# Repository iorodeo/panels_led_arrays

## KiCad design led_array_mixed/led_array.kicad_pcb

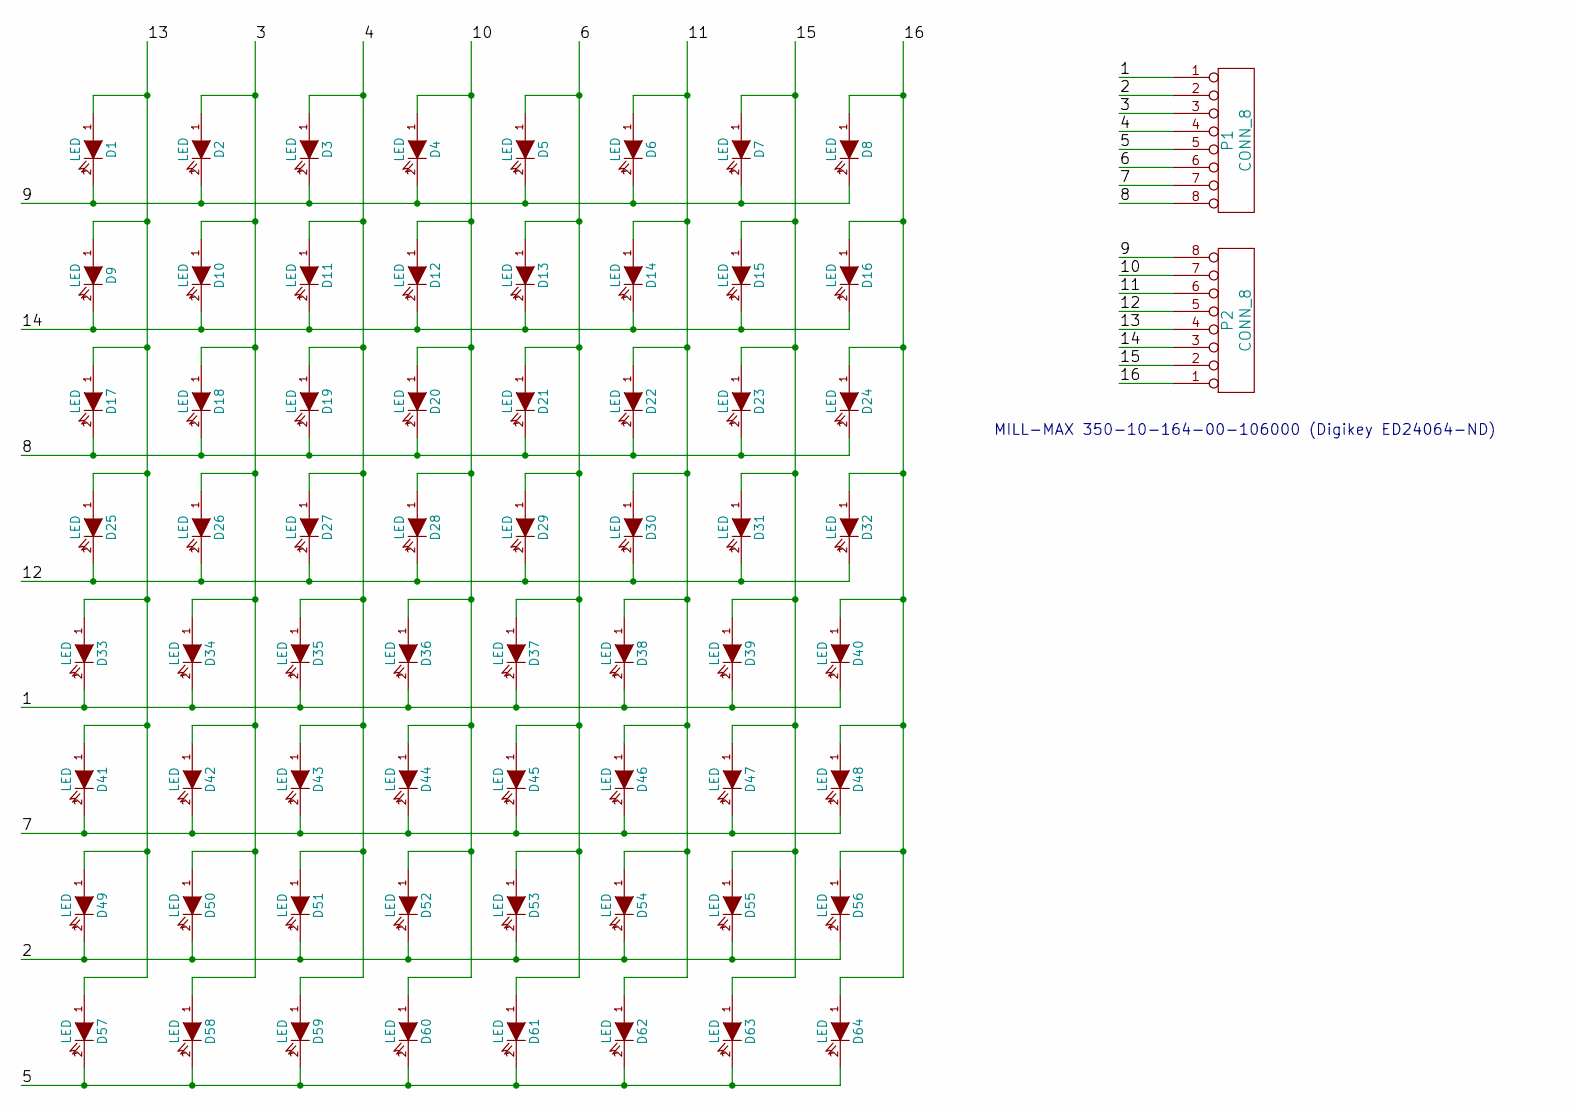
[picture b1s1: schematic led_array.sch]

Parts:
D1, D2, D3, D4, D5, D6, D7, D8, D9, D10, D11, D12, D13, D14, D15, D16, D17, D18, D19, D20, D21, D22, D23, D24, D25, D26, D27, D28, D29, D30, D31, D32, D33, D34, D35, D36, D37, D38, D39, D40, D41, D42, D43, D44, D45, D46, D47, D48, D49, D50, D51, D52, D53, D54, D55, D56, D57, D58, D59, D60, D61, D62, D63, D64: LED
P1, P2: CONN_8

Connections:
/1: D33.2 (K), D34.2 (K), D35.2 (K), D36.2 (K), D37.2 (K), D38.2 (K), D39.2 (K), D40.2 (K), P1.1
/2: D49.2 (K), D50.2 (K), D51.2 (K), D52.2 (K), D53.2 (K), D54.2 (K), D55.2 (K), D56.2 (K), P1.2
/3: D2.1 (A), D10.1 (A), D18.1 (A), D26.1 (A), D34.1 (A), D42.1 (A), D50.1 (A), D58.1 (A), P1.3
/4: D3.1 (A), D11.1 (A), D19.1 (A), D27.1 (A), D35.1 (A), D43.1 (A), D51.1 (A), D59.1 (A), P1.4
/5: D57.2 (K), D58.2 (K), D59.2 (K), D60.2 (K), D61.2 (K), D62.2 (K), D63.2 (K), D64.2 (K), P1.5
/6: D5.1 (A), D13.1 (A), D21.1 (A), D29.1 (A), D37.1 (A), D45.1 (A), D53.1 (A), D61.1 (A), P1.6
/7: D41.2 (K), D42.2 (K), D43.2 (K), D44.2 (K), D45.2 (K), D46.2 (K), D47.2 (K), D48.2 (K), P1.7
/8: D17.2 (K), D18.2 (K), D19.2 (K), D20.2 (K), D21.2 (K), D22.2 (K), D23.2 (K), D24.2 (K), P1.8
/9: D1.2 (K), D2.2 (K), D3.2 (K), D4.2 (K), D5.2 (K), D6.2 (K), D7.2 (K), D8.2 (K), P2.8
/10: D4.1 (A), D12.1 (A), D20.1 (A), D28.1 (A), D36.1 (A), D44.1 (A), D52.1 (A), D60.1 (A), P2.7
/11: D6.1 (A), D14.1 (A), D22.1 (A), D30.1 (A), D38.1 (A), D46.1 (A), D54.1 (A), D62.1 (A), P2.6
/12: D25.2 (K), D26.2 (K), D27.2 (K), D28.2 (K), D29.2 (K), D30.2 (K), D31.2 (K), D32.2 (K), P2.5
/13: D1.1 (A), D9.1 (A), D17.1 (A), D25.1 (A), D33.1 (A), D41.1 (A), D49.1 (A), D57.1 (A), P2.4
/14: D9.2 (K), D10.2 (K), D11.2 (K), D12.2 (K), D13.2 (K), D14.2 (K), D15.2 (K), D16.2 (K), P2.3
/15: D7.1 (A), D15.1 (A), D23.1 (A), D31.1 (A), D39.1 (A), D47.1 (A), D55.1 (A), D63.1 (A), P2.2
/16: D8.1 (A), D16.1 (A), D24.1 (A), D32.1 (A), D40.1 (A), D48.1 (A), D56.1 (A), D64.1 (A), P2.1

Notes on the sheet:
MILL-MAX 350-10-164-00-106000 (Digikey ED24064-ND)

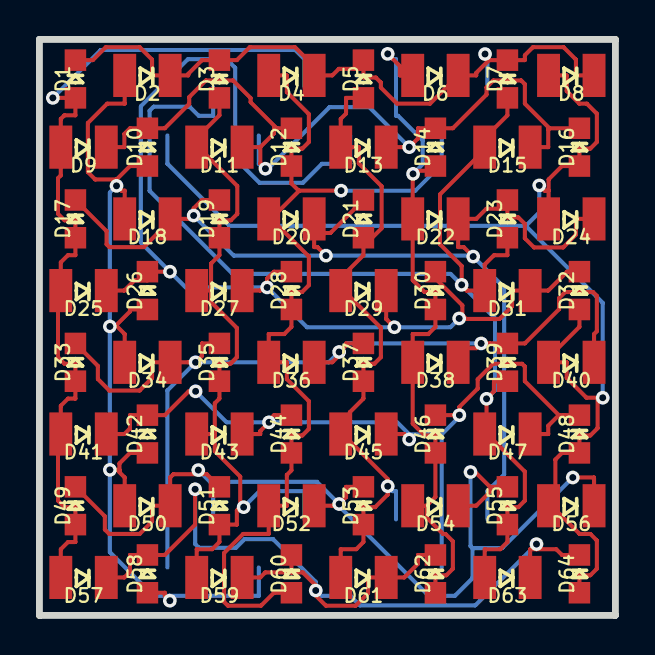
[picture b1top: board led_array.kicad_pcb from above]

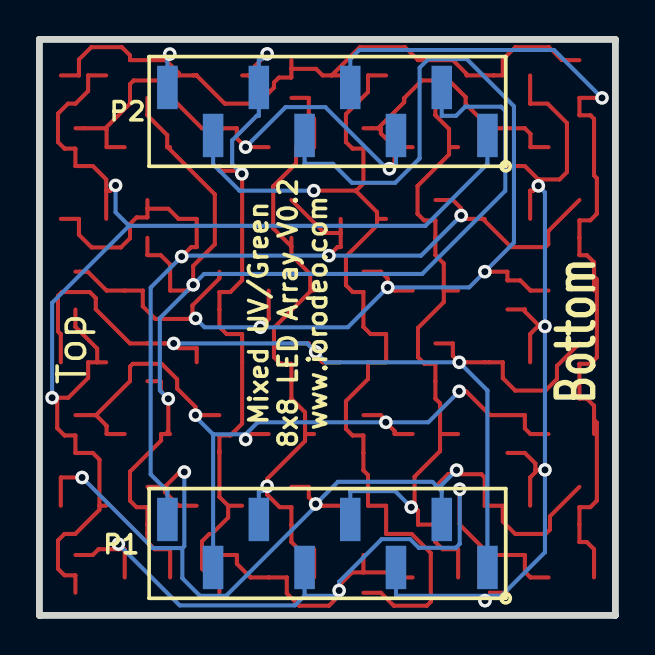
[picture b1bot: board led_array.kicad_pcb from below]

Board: 2 copper layers, 32.0 x 32.0 mm, 66 parts (2 on the bottom side), 16 nets.

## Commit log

2013-02-12 Project creation.
2013-02-12 Added license file.
2013-02-13 Fixed missing solder mask on 3mm led array.
2013-02-13 Changed license from apache to creative commons. Initial choise of apache was a mistake as this is a hardware project.
2013-02-28 Added pass_thru_panel.
2013-04-24 Added gerber files and spacer design for 3mm led array.
2013-11-20 Added mask design for 5mm led array.
2014-09-16 Added mixed smd0805 and smd1411 led arry.
2014-09-16 Routed new mixed UV/Green LED array.
2014-09-16 Removed old gerbers.
2014-09-16 Added gerber files for mix led array design.
2014-09-17 Added .zip of mixed led array v0.1 gerber files.
2014-10-21 Added BOM, remade gerber files for turnkey assembly quotation.
2014-10-21 Modified BOM.
2014-10-21 Put copy of bom in with version specific gerbers.
2014-12-22 Added note about inverting labels.
2014-12-22 Added gerber files for version 0.2 of the design. In version 0.1 the TOP and BOTTOM labels where swapped. Version 0.2 corrects this issue.
2015-01-01 Added positions csv file.
2016-07-13 Modified BOM. Added SMD pin arrays.
